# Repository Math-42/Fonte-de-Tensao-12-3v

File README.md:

# Fonte de tensão ajustável

##  Lista de componentes

|Quantidade| Componente        | Especificações/tipo | Valor |
| :---     | :---              |     :---:           | :---  |
|    1     | [Resistor](https://www.baudaeletronica.com.br/resistor-2k2-5-1-4w.html) 		   | 2K2Ω                |   R$0,08    |
|    1     | [Capacitor](https://www.baudaeletronica.com.br/capacitor-eletrolitico-470uf-35v.html)		   | 470 µF              |  R$1,09     |
|    1     | [Resistor](https://www.baudaeletronica.com.br/resistor-1k-5-1-4w.html)		   | 1KΩ                  |     R$0,14  |  
|    1     | [Resistor](https://www.baudaeletronica.com.br/resistor-1k1-1-2w.html)		   | 1K1Ω                  |     R$0,14  | 
|    4     | [Diodo](https://www.baudaeletronica.com.br/diodo-6a10.html)			   | [6A10](https://storage.googleapis.com/baudaeletronicadatasheet/6A10.pdf)			 |     R$0,86   |
|    1     | [Diodo Zener](https://www.baudaeletronica.com.br/diodo-zener-1n4743-13v-1w.html)	   | [1N4743](https://www.baudaeletronica.com.br/diodo-zener-1n4743-13v-1w.html)		     |   R$0,20    |
|    1     | [LED](https://www.baudaeletronica.com.br/led-de-alto-brilho-vermelho.html)			   | Alto Brilho         |  R$0,24     |
|    1     | [Potenciômetro](https://www.baudaeletronica.com.br/potenciometro-linear-de-5k-5000.html)   | 5KΩ              |     R$1,09   | 
|    1     | [Transistor](https://www.baudaeletronica.com.br/transistor-npn-bc337.html)       | [BC337](https://storage.googleapis.com/baudaeletronicadatasheet/BC337.PDF)             |    R$0,17   |
|    1     | [Transformador](https://www.baudaeletronica.com.br/transformador-trafo-1a-24v.html)   | 24V ou +12V/-12V    |   R$36,00    | 
| 1 | [Chave gangorra](https://www.baudaeletronica.com.br/mini-chave-gangorra-kcd11-101-2-terminais-verde.html)| - | R$0,94
| 3 | [Conector](https://www.baudaeletronica.com.br/borne-2-polos-kf-301-2t.html)| Borne | R$0,76
| 1 | [*Display](https://br.banggood.com/Geekcreit-Mini-Digital-Voltmeter-Ammeter-DC-100V-10A-Voltmeter-Current-Meter-Tester-BlueRed-Dual-LED-Display-p-1416489.html?gpla=1&gmcCountry=BR&currency=BRL&createTmp=1&utm_source=googleshopping&utm_medium=cpc_bgs&utm_content=lijing&utm_campaign=ssc-brg-all-1014-newcustom-re0327&ad_id=389344072730&gclid=Cj0KCQjwz4z3BRCgARIsAES_OVd-WYtEYyOGJNCb5vra89DurCnhwjkIOx-fQ4ghT_pFcfvKb8wn5VMaAvMDEALw_wcB&cur_warehouse=CN)| - | R$15,58

* *Obs: O display é opcional

## Imagens

### Simulação da fonte
* link: http://tinyurl.com/y8wweeaz

### Diagrama da fonte

### Esquemático da fonte

### Parte de baixo da placa de circuito

### Topo da placa de circuito 

* Obs: No eagle, top e bottom estão invertidos, o que pode causar um pouco de confusão

## [Vídeo Explicativo](https://drive.google.com/file/d/1FfJFXwUXuSc7ZVDYow56NexWSYLpmYIj/view?usp=sharing)
* Obs: é necessário utilizar o email USP
* Os arquivos do eagle podem ser encontrados na pasta eagle

## Participantes

* **Matheus Vieira Gonçalves** - [Math-42](https://github.com/Math-42)

* **Pedro Henrique Dias Junqueira**  - [pedrohdjs](https://github.com/pedrohdjs)

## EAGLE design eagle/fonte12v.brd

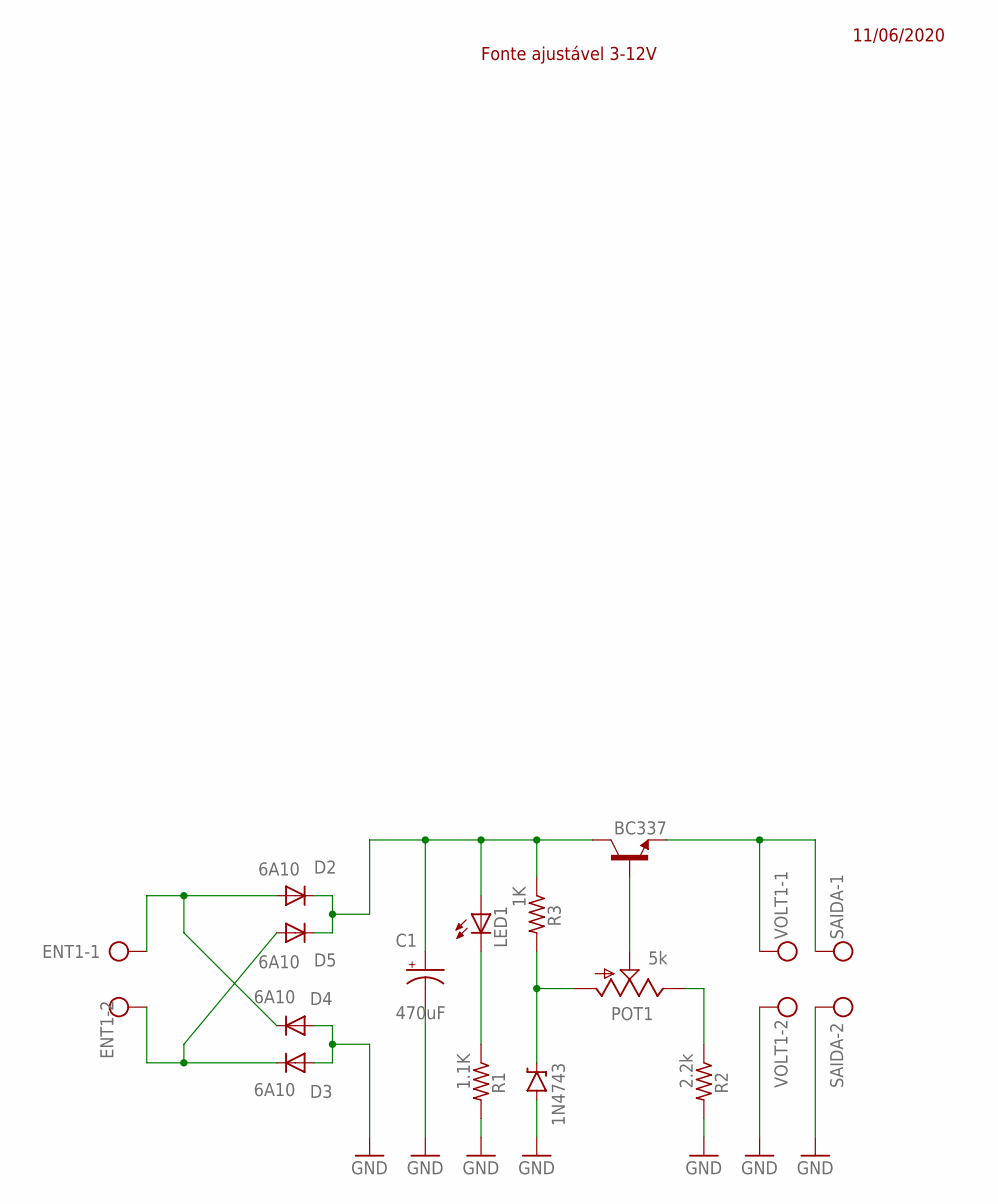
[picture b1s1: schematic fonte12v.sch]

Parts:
1N4743: BZT52; DIODE-BZT52
C1: 470uF; E5-13
D2, D3, D4, D5: 6A10; DO41-10
ENT1: AK500/2-H
LED1: LED5MM
POT1: 5k; ALPS_POT
R1: 1.1K; 0805-THM
R2: 2.2k; 0805-THM
R3: 1K; 0805-THM
SAIDA: AK500/2-H
T1: BC337; TO92
VOLT1: AK500/2-H

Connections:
GND: 1N4743.A, C1.-, D3.A, D4.A, R1.2, R2.2, SAIDA.2, VOLT1.2
unnamed: POT1.P$2 (S), T1.2 (B)
unnamed: LED1.K (C), R1.1
unnamed: POT1.P$1 (E), R2.1
unnamed: SAIDA.1, T1.1 (E), VOLT1.1
unnamed: 1N4743.C, POT1.P$3 (A), R3.2
unnamed: D3.C, D5.A, ENT1.2
unnamed: D2.A, D4.C, ENT1.1
unnamed: C1.+, D2.C, D5.C, LED1.A, R3.1, T1.3 (C)

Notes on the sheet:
Fonte ajustável 3-12V
11/06/2020

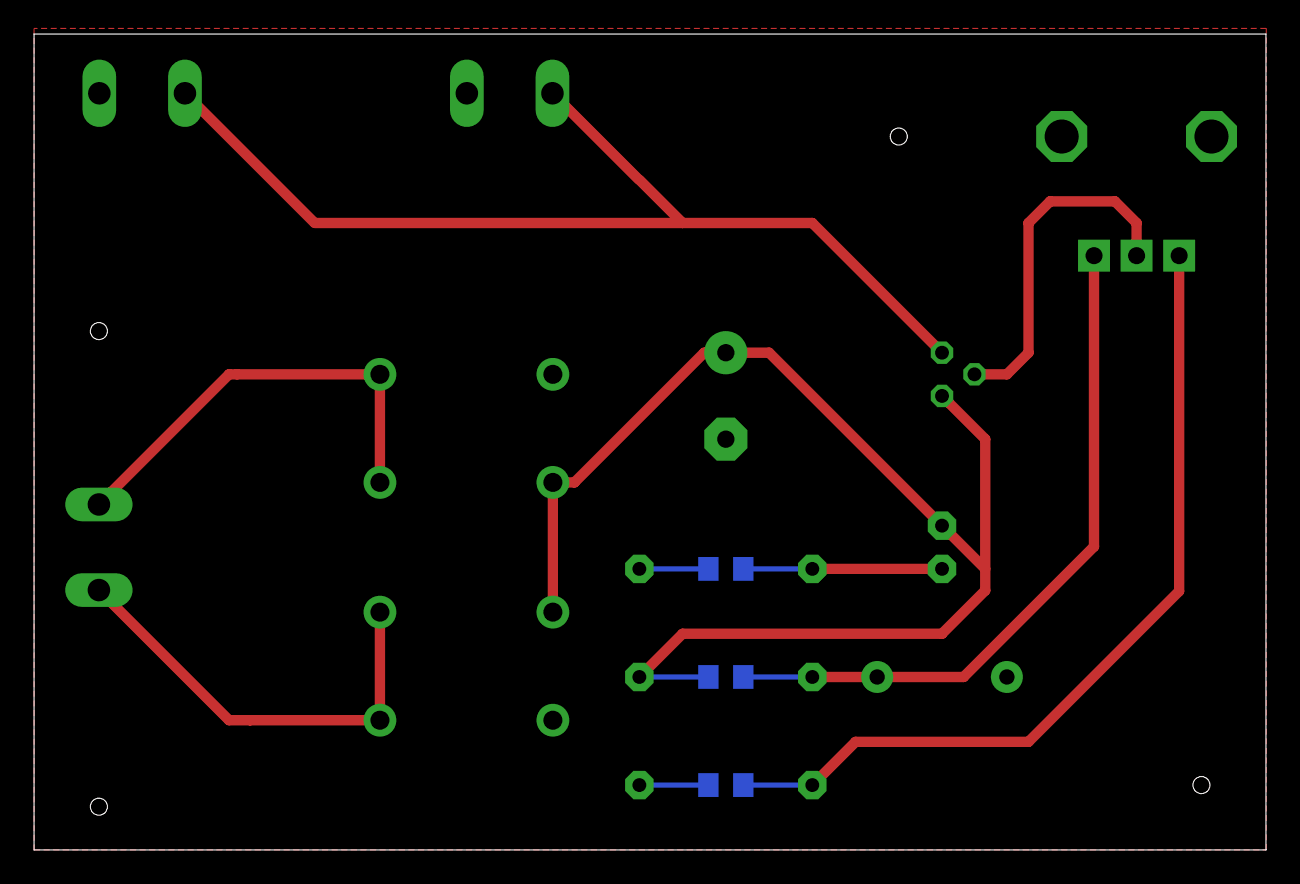
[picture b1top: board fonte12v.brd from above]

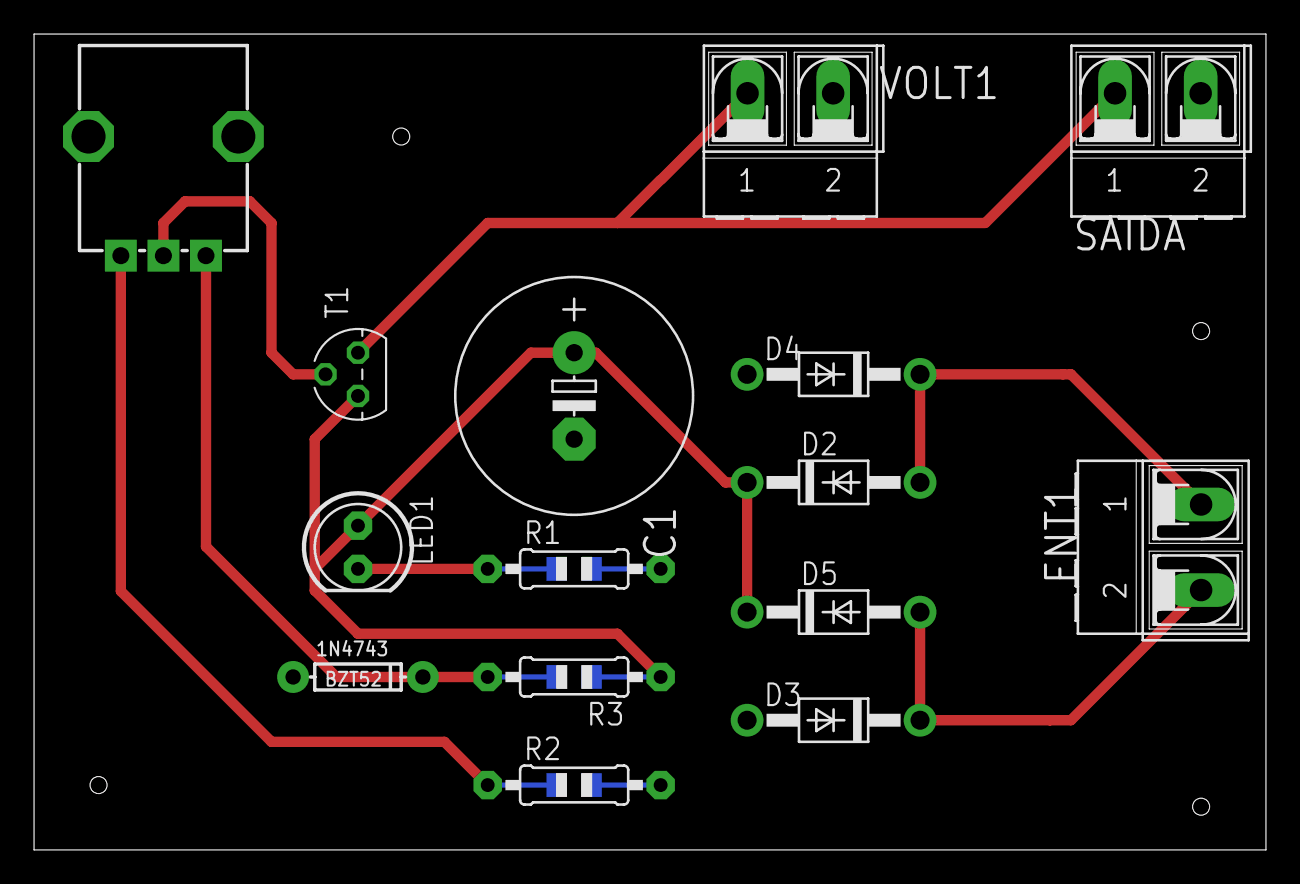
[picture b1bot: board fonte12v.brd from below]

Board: 2 copper layers, 72.4 x 47.9 mm, 15 parts (15 on the bottom side), 9 nets.

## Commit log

2020-06-12 readme
2020-06-12 primeiras imagens
2020-06-12 correção readme
2020-06-12 correção caracteres
2020-06-12 correção caracteres especiais
2020-06-12 adicionando gif
2020-06-12 corrigindo
2020-06-12 atualização da simulação
2020-06-12 correção de link
2020-06-12 Voltimetro + amperimetro
2020-06-12 Conector borne
2020-06-15 Corrigindo nicks dos participantes
2020-06-29 Correção nas imagens
2020-06-29 Correção nas imgens
2020-06-29 apagando push errado
2020-06-29 Adicionando esquematico
2020-06-29 Correção no resistor e no led
2020-06-29 Correção do ratio do transformador
2020-06-29 Correção link 1k
2020-06-29 Chave gangorra mais simples
2020-06-29 corrigindo resistor
2020-06-29 att link simulacao
2020-06-29 att gif
2020-06-29 video explicativo
2020-06-29 obs email usp
2020-06-29 eagle
2020-06-29 alteracao no diagrama
2020-07-01 novo link video

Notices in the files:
parts and their libraries:
SparkFun-DiscreteSemi: Licensing: Creative Commons ShareAlike 4.0 International - https://creativecommons.org/licenses/by-sa/4.0
